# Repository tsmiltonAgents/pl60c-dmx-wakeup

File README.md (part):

# PL60C DMX wake-up lamp controller

A small ESP32-S3 board that drives the wired DMX512 input of a **Neewer PL60C** panel light so the
light can be ramped up slowly in the morning (sunrise alarm). Rev A, 2026-09-02.

Everything in this repository is generated by scripts (`./build.sh`): schematic, PCB, autorouting,
design-rule checks, Gerbers, and the JLCPCB BOM / pick-and-place files. The design passes KiCad ERC and
DRC with zero errors, the schematic and PCB netlists are cross-checked against the single source of
truth (`hw/design.py`), and every part number has been verified in stock on LCSC/JLCPCB.

| | |
|---|---|
| Board | 80 x 54 mm, 2 layers, 1.6 mm FR-4, all parts on the top side |
| MCU | ESP32-S3-WROOM-1-N16R8 (Wi-Fi + BLE, native USB) |
| DMX out | 5-pin XLR female (Neutrik NC5FAH) **and** a 3-way screw terminal for a pigtail |
| Power | USB-C, 5 V, 1 A resettable fuse, 3.3 V LDO |
| UI | RESET, BOOT, USER buttons, WS2812B RGB status LED, magnetic buzzer (alarm fallback) |
| Extras | I2C/GPIO expansion header (RTC, light sensor), UART0 header |
| Files to order | `production/pl60c_dmx_gerbers.zip`, `production/pl60c_dmx_bom_jlcpcb.csv`, `production/pl60c_dmx_cpl_jlcpcb.csv` |
| Mini variant | 38.5 x 29 mm, 4 layers, both sides, same circuit and pin map: see section 8 and `production_mini/` |

Status: **designed, reviewed and verified in software, not yet manufactured or bench-tested.** Read the
"Before you order" section and `docs/REVIEW.md` (design review: 3 wiring/spec bugs found and fixed).

---

## 1. How the light is controlled

### 1.1 The PL60C's DMX port (verified from Neewer's manual and DMX chart)

* Connectors on the bottom edge of the lamp head: `DMX-IN` = **5-pin XLR male** panel socket,
  `DMX-OUT` = 5-pin XLR female (pass-through for daisy-chaining).
* Pinout: pin 1 = signal common (0 V), pin 2 = Data−, pin 3 = Data+, pins 4 and 5 unused.
* Enable DMX on the light: long-press MODE/MENU, set `DMX ON/OFF` = ON, then `DMX ADDR` (001–512, default 1).
* On loss of the DMX signal the light **holds the last look** (no timeout). The controller must therefore
  keep streaming frames; when you want the light off, send intensity 0 rather than stopping the stream.
* No RDM support is documented. The port is not documented as isolated.

This board is the DMX **transmitter**, so it has a 5-pin XLR **female** socket (ANSI E1.11 convention).
A normal 5-pin DMX cable (male–female) goes from this board to the light's `DMX-IN`.

### 1.2 PL60C channel map (one fixed personality)

Channel numbers are relative to the DMX start address `n` set on the light. Channel `n` selects the mode,
`n+1` is always intensity, the rest depend on the mode. The FX mode uses up to 9 channels, so treat the
light as a 9-channel fixture.

| ch n value | Mode | n+1 | n+2 | n+3 | n+4 … n+8 |
|---|---|---|---|---|---|
| 0–31 | **CCT** | Intensity 0–100 % | Colour temperature 2500–10000 K | G/M −50…+50 | – |
| 32–63 | HSI | Intensity | Hue 0–360° | Saturation 0–100 % | – |
| 64–95 | FX | Intensity | Effect select | effect parameters | effect parameters |
| 96–127 | GEL | Intensity | Gel brand | Gel index | – |
| 128–159 | RGBCW | Intensity | Red | Green | Blue, Cool white, Warm white |
| 160–191 | XY | Intensity | x | y | – |

For a sunrise, CCT mode is the natural choice: ramp `n+1` from 0 to the target and, if you like, sweep
`n+2` from warm (2500 K) towards neutral as the intensity rises. Sources are listed at the end.

### 1.3 DMX512 on the wire

DMX512 is EIA-485 at 250 kbit/s, 8 data bits, no parity, 2 stop bits. A frame is: BREAK (≥ 92 µs, use
176 µs) → MARK-AFTER-BREAK (≥ 12 µs) → start code 0x00 → up to 512 slot bytes, then repeat at roughly
40–44 Hz. Data+ (pin 3) is the RS-485 **A** line, Data− (pin 2) is **B**, pin 1 is the common. A 120 Ω
terminator belongs only at the far end of the cable (the last fixture), never at the transmitter.

---

## 2. Hardware design

Full-size PDF: `production/pl60c_dmx_schematic.pdf`.

### 2.1 Blocks

**USB-C input and 3.3 V rail.** 16-pin USB-C receptacle (HRO TYPE-C-31-M-12) with 5.1 kΩ CC pull-downs
so any USB-C charger or host supplies 5 V. A 1 A hold / 1.8 A trip PTC (F1) protects the board, a
USBLC6-2SC6 (U4) clamps ESD on D+/D−/VBUS, and an AMS1117-3.3 (U2, 1 A) makes 3.3 V with 10 µF on both
sides. Budget: ESP32-S3 Wi-Fi peaks ≈ 0.5 A, buzzer ≈ 0.1 A average, LED < 60 mA.

**ESP32-S3-WROOM-1-N16R8 (U1).** 16 MB flash, 8 MB PSRAM, on-module PCB antenna. The antenna end of the
module hangs 6 mm past the top board edge, which is Espressif's preferred placement (no copper anywhere
near the antenna). USB D+/D− go straight to GPIO20/GPIO19: the S3's built-in USB-Serial/JTAG gives
programming, console and debugging with no bridge chip. EN has the standard 10 kΩ + 1 µF reset delay and
the RESET button; GPIO0 has a 10 kΩ pull-up and the BOOT button (hold BOOT, tap RESET to force the
ROM downloader, or just use `esptool` over USB which does it automatically).

**DMX transmitter (U3, SP3485EN).** 3.3 V RS-485 half-duplex transceiver, pin-compatible with MAX3485.
DI ← GPIO17 (UART TX), RO → GPIO18 (UART RX), DE and /RE tied together to GPIO16 with a 10 kΩ pull-down,
so the line is only driven once firmware asserts DE (keeps the bus quiet during boot/flash). A → XLR
pin 3 (Data+), B → XLR pin 2 (Data−), XLR pin 1 → GND. A PSM712 asymmetric TVS array (D1, +12 V / −7 V,
the RS-485 standard part) clamps surges on both lines. R6 (120 Ω) is fitted **only** if you ever want this
board to terminate a line; it is marked DNP and JLCPCB will not place it. The same three signals are on
screw terminal J3 (GND, D−, D+) so you can wire a cable pigtail instead of using the XLR.

**User interface.** WS2812B-2020-V6 RGB LED (D2) on GPIO48 through 330 Ω, powered from 3.3 V (the V6
silicon is specified for 3.3 V supply, VIH = 0.55 VDD). USER button on GPIO5 with a 10 kΩ pull-up
(snooze / manual on). Magnetic buzzer BZ1 (MLT-8530, passive, 2.7 kHz resonant, 16 Ω) driven from the
5 V rail through a 10 Ω series resistor (R10, limits the coil to its 3.6 V rating) by an S8050 NPN (Q1,
SOT-23, base via 470 Ω from GPIO6) with a B5819W Schottky flyback diode (D3) across the coil.

**Expansion.** J4: 3V3, GND, GPIO8 (SDA), GPIO9 (SCL), GPIO10, GPIO11 (e.g. a DS3231 RTC or an ambient
light sensor). J5: 3V3, GND, GPIO43 (TXD0), GPIO44 (RXD0). Four M3 mounting holes.

### 2.2 Pin map (also in `firmware/pins.h`)

| Function | GPIO | Notes |
|---|---|---|
| DMX TX (SP3485 DI) | 17 | UART1 TX |
| DMX RX (SP3485 RO) | 18 | UART1 RX, only for RDM/monitoring |
| DMX DE / /RE | 16 | HIGH = transmit; 10 kΩ pull-down |
| USB D− / D+ | 19 / 20 | native USB-Serial/JTAG |
| BOOT button | 0 | active low, strapping pin |
| USER button | 5 | active low, 10 kΩ pull-up |
| WS2812B data | 48 | 330 Ω series, LED at 3.3 V |
| Buzzer | 6 | NPN low-side switch, PWM 2.7 kHz |
| I2C SDA / SCL | 8 / 9 | header J4 |
| Spare | 10 / 11 | header J4 |
| UART0 TX / RX | 43 / 44 | header J5 |

Unused module pins are left unconnected. GPIO35–37 are reserved by the octal PSRAM of the R8 module
and GPIO3/45/46 are strapping pins; none of them is used.

### 2.3 Layout

USB-C on the left edge, XLR on the right edge with its flange over the board edge, buttons and the LED
along the bottom edge for an enclosure front panel, the terminal block also on the bottom edge.
Ground pours on both layers with stitching vias, 0.25 mm signal tracks, 0.4 mm power tracks,
0.15 mm clearance, 0.7 / 0.35 mm vias: all comfortably inside JLCPCB's 2-layer capability.
The USB-C data-pair escape is hand-routed (the router cannot do the D+/D− pair swap at 0.5 mm pitch);
the rest is autorouted by Freerouting and then checked by KiCad DRC.

---

## 3. Firmware guidance (no firmware is included, by design)

The hardware was designed so that the standard **[esp_dmx](https://github.com/someweisguy/esp_dmx)**
library works unmodified: `dmx_set_pin(DMX_NUM_1, PIN_DMX_TX, PIN_DMX_RX, PIN_DMX_DE)` and then
`dmx_write()` + `dmx_send()` at 40–44 Hz. It handles the break/MAB timing with the UART hardware.

Suggested behaviour:

1. Boot, connect to Wi-Fi, sync time by SNTP (add a DS3231 on J4 if you want time without Wi-Fi).
2. Stream a DMX frame continuously (44 Hz). Idle: `ch1 = 0` (CCT mode), `ch2 = 0` (intensity 0).
   Never stop the stream: the PL60C holds the last look on signal loss.
3. Sunrise: over 20–30 min raise `ch2` from 0 → target with a perceptual (gamma ≈ 2.2) curve, optionally
   sweep `ch3` from 2500 K towards 4000–5600 K. After the ramp hold, then optionally sound the buzzer
   (2.7 kHz square wave on GPIO6, 50 % duty, short beeps) until USER is pressed.
4. USER button: short press = snooze / cancel, long press = manual light toggle. BOOT can be a second
   button after boot. RGB LED: breathing colours for state (idle / ramping / alarm / no Wi-Fi).
5. Set the light's `DMX ADDR` to 1 so the controller's channels 1–9 map directly.

Provisioning, OTA and a web UI are the usual ESP-IDF / Arduino-ESP32 fare; the S3's USB CDC console is
available on the USB-C port without any extra hardware.

---

## 4. Ordering from JLCPCB

Files in `production/`:

| File | Purpose |
|---|---|
| `pl60c_dmx_gerbers.zip` | Gerber RS-274X (Protel extensions) + Excellon drills, JLCPCB settings |
| `pl60c_dmx_bom_jlcpcb.csv` | BOM in JLCPCB format (Comment, Designator, Footprint, LCSC Part #) |
| `pl60c_dmx_cpl_jlcpcb.csv` | Pick-and-place, rotations corrected with the JLCKicadTools database |
| `pl60c_dmx_cpl_kicad_rotation.csv` | Same, with raw KiCad rotations, in case the preview shows parts turned |
| `pl60c_dmx_bom_full.csv` | Engineering BOM incl. DNP and mechanical parts |
| `pl60c_dmx_schematic.pdf`, `pl60c_dmx_pcb_top.pdf`, `pl60c_dmx_pcb_bottom.pdf`, `pl60c_dmx.step` | documentation / mechanical |

Steps:

1. jlcpcb.com → *Order now* → upload `pl60c_dmx_gerbers.zip`. Options: 2 layers, 80 x 54 mm, 1.6 mm,
   any colour, HASL (lead-free) or ENIG, 1 oz copper, "Remove order number: specify location" is not
   needed (no marker placed; choose "Yes" if you dislike the number).
2. Turn on **PCB Assembly**, top side, then upload `pl60c_dmx_bom_jlcpcb.csv` and
   `pl60c_dmx_cpl_jlcpcb.csv`.
3. In the parts step all 25 BOM lines resolve to the LCSC numbers below. R6 is intentionally absent (DNP).
4. **Check the placement preview carefully** for rotation of U2 (SOT-223), U3 (SOIC-8), D1/Q1 (SOT-23),
   J1 (USB-C), D2 (WS2812B), J2 (XLR) and J3 (terminal). JLCPCB's orientation conventions differ from
   KiCad's per package; if any polarised part looks turned, re-upload
   `pl60c_dmx_cpl_kicad_rotation.csv` or rotate it in their editor. Pin 1 of the module is the
   top-left pad when the antenna points up.
5. Through-hole parts (XLR, terminal block, headers) are "extended" parts assembled by hand at JLCPCB;
   they add a small per-part fee. If you prefer, delete J2/J3/J4/J5 from the BOM and solder them yourself.

### 4.1 Bill of materials (all verified in stock on LCSC on 2026-09-02, `tools/check_lcsc.py`)

| Ref | Part | LCSC | JLC type |
|---|---|---|---|
| U1 | ESP32-S3-WROOM-1-N16R8 | C2913202 | extended |
| U2 | AMS1117-3.3, SOT-223 | C6186 | basic |
| U3 | SP3485EN-L/TR, SOIC-8 | C8963 | basic |
| U4 | USBLC6-2SC6, SOT-23-6 | C7519 | extended |
| D1 | PSM712-LF-T7 TVS, SOT-23 | C32677 | basic |
| D2 | WS2812B-2020-V6 RGB LED | C52917434 | extended |
| D3 | B5819W Schottky, SOD-123 | C8598 | basic |
| Q1 | S8050 NPN, SOT-23 (B-E-C) | C2146 | basic |
| F1 | PTC 1 A hold, 1206 | C5358568 | extended |
| J1 | USB-C 16P, HRO TYPE-C-31-M-12 | C165948 | extended |
| J2 | Neutrik NC5FAH XLR-5 female, PCB horizontal | C368501 | extended (low stock, ~130) |
| J3 | KF128-5.08-3P screw terminal | C474953 | extended |
| J4 / J5 | 2.54 mm headers 1x6 / 1x4 | C37208 / C124378 | extended |
| SW1–SW3 | TS-1187A-B-A-B tactile 5.1 mm | C318884 | basic |
| BZ1 | MLT-8530 magnetic buzzer | C94599 | extended |
| C1, C4 | 10 µF 25 V 0805 | C15850 | basic |
| C2 | 22 µF 25 V 0805 | C45783 | basic |
| R10 | 10 Ω 1206 250 mW | C17903 | basic |
| C6 | 1 µF 50 V 0805 | C28323 | basic |
| C3, C5, C7, C8 | 100 nF 50 V 0603 | C14663 | basic |
| R1, R2 | 5.1 kΩ 0603 | C23186 | basic |
| R3, R4, R5, R7 | 10 kΩ 0603 | C25804 | basic |
| R8 | 330 Ω 0603 | C23138 | basic |
| R9 | 470 Ω 0603 | C23179 | basic |
| R6 | 120 Ω 0603, **DNP** | C22787 | – |

If the NC5FAH is out of stock: CAX **XLR-5M-24WP** (C53431204, same NC5FAH footprint, female despite the
name) or order the Neutrik separately and hand-solder it. Rough parts cost per board is about USD 15
(ESP32 ≈ 5, XLR ≈ 6), plus JLCPCB's PCB and assembly fees.

### 4.2 Before you order

* This is a rev A that has only been verified by simulation-free checks (ERC, DRC, netlist, Gerber
  review, part stock). The circuit follows Espressif's and the transceiver vendor's reference designs
  closely, but a first build should be treated as a prototype.
* The DMX port is **not galvanically isolated** (same as most hobby DMX interfaces). The PL60C runs from
  its own 19.6 V PSU; keep the controller on a separate USB supply and you have a normal
  ground-referenced link, which is how the light's own wired console connection works. An isolated
  variant (ADM2483 + B0505S) would add ~USD 7 and a second transceiver footprint; not done in rev A.
* USB-C receptacle mechanical: the connector body is placed with its front lip 0.55 mm proud of the
  board edge, per the HRO drawing. Check it against your enclosure.

---

## 5. Hooking it up

1. Flash firmware over the USB-C port (native USB, no driver hassle on macOS/Linux).
2. Cable: 5-pin XLR male → female DMX cable from this board's `DMX OUT` to the light's `DMX-IN`.
   Or wire a cable to J3: `GND` → XLR pin 1, `D−` → pin 2, `D+` → pin 3.
3. On the light: `DMX ON`, `DMX ADDR = 001`.
4. If the light is the only fixture and the cable is longer than a few metres, fit a 120 Ω terminator
   plug in the light's `DMX-OUT`. Do not fit R6 on this board.

---

## 6. What was verified

| Check | Result |
|---|---|
| Design review against datasheets (`docs/REVIEW.md`) | 14 items; 3 bugs found and fixed (SOT-23 transistor pinout, LED supply spec, buzzer overdrive) |
| KiCad ERC on the generated schematic | 0 findings |
| Schematic netlist vs `hw/design.py` | 27/27 nets identical |
| PCB pad-to-net vs `hw/design.py` | 27/27 nets identical |
| KiCad DRC (clearance 0.15 mm, edge 0.3 mm, hole-to-hole 0.5 mm, courtyards, silkscreen) | 0 errors; 6 warnings, all "silkscreen clipped by board edge" from the three connectors that deliberately overhang the edge |
| Unrouted connections | 0 |
| Gerbers rendered independently with gerbv (copper, silk, mask, paste, outline, drills) | match the KiCad board, see `docs/gerber_*_check.png` |
| Drill file | 151 plated + 8 non-plated holes, smallest 0.30 mm (module thermal vias enlarged from the library's 0.2 mm to suit JLCPCB) |
| LCSC stock / package for every part number | all in stock, packages match footprints (`tools/check_lcsc.py`) |
| Datasheets checked against footprints | TS-1187A vs Alps SKQG land pattern, MLT-8530 pad layout, KF128 pin size (holes set to 1.4 mm), NC5FAH (KiCad footprint is for this exact part) |

---

## 7. Repository layout and regenerating

```
hw/design.py        single source of truth: parts, LCSC numbers, nets, schematic and PCB placement
hw/design_mini.py   the MINI variant (same circuit, different parts/placement); hw/variant.py selects it
hw/gen_sch.py       KiCad 10 schematic writer (labels + power symbols, ERC-clean)
hw/gen_pcb.py       pcbnew script: board outline, footprints, nets, rules, pours, GND stitching, USB escape
hw/route.py         Freerouting driver (DSN export, autoroute, SES import, zone fill)
hw/fix_gnd.py       post-route ground fixer + dangling via cleanup
tools/export.py     Gerbers/drill, JLCPCB BOM + CPL, PDFs, renders, STEP
tools/verify_*.py   netlist consistency checks
tools/check_lcsc.py live stock check of every LCSC part number
pcb/                the generated KiCad project (open pl60c_dmx.kicad_pro in KiCad 10)
production/         everything JLCPCB needs
docs/               images used in this README
firmware/pins.h     pin map and DMX constants for the firmware author
build.sh            full pipeline; autocommit.sh commits and pushes every 2 minutes
```

Regenerate with `./build.sh` (rev A) or `./build.sh mini`. Requirements: KiCad 10.0.x app bundle at `/Applications/KiCad`
(its bundled Python is used for `pcbnew`), Java 25+ (`brew install openjdk`) and
`tools/freerouting.jar` (Freerouting 2.3.0, download from its GitHub releases), plus `gerbv` if you want
the Gerber check images. Edit `hw/design.py`, never the KiCad files (they are overwritten).

---

## 8. MINI variant (38.5 x 29 mm, 4 layers, both sides)

Same circuit, same GPIO map, one quarter of the area (1120 mm² vs 4320 mm²). Files: `production_mini/`
(`pl60c_dmx_mini_gerbers.zip`, `pl60c_dmx_mini_bom_jlcpcb.csv`, `pl60c_dmx_mini_cpl_jlcpcb.csv`),
KiCad project `pcb/pl60c_dmx_mini.*`, source `hw/design_mini.py`, build with `./build.sh mini`.

What changed to get there:

| | rev A | mini |
|---|---|---|
| Module | ESP32-S3-WROOM-1-N16R8 (18 x 25.5 mm) | **ESP32-S3-MINI-1-N8** (15.4 x 20.5 mm, C2913206), antenna off the left edge |
| Layers / sides | 2 layers, top only | **4 layers** (JLC04161H-7628 stack: signal, solid GND plane, signal + GND pour, signal), parts on **both sides** |
| XLR-5 female | on board | **on board** (Neutrik NC5FAH, right edge; its flange holes mount the board) |
| Passives | 0603 / 0805 | **0402** (all JLCPCB Basic), 10 µF in 0603 |
| LDO | AMS1117 SOT-223 | **AP2112K-3.3** SOT-23-5, 600 mA (C51118) |
| RGB LED | WS2812B-2020-V6 | same |
| Buttons | RESET, BOOT, USER (5.1 mm) | **BOOT, USER** (3.9 x 3 mm TS-1088, Basic); reset = re-plug USB or EN via the 10 k/1 µF network |
| Buzzer | on board | **off board**: driver kept (S8050 + 10 Ω + flyback), solder a passive magnetic buzzer to the `BZ+`/`BZ-` pads |
| Pigtail terminal, headers, mounting holes | yes | dropped; I2C expansion on 4 test pads (`3V3 GND SDA SCL`), UART0 not brought out (USB console) |
| PTC | 1 A 1206 | same |

Top side: module, USB-C, XLR, two buttons, RGB LED. Bottom side: everything else. The USB-C body
protrudes 0.55 mm from the bottom edge, the XLR flange protrudes from the right edge, and the module
antenna hangs 4.5 mm off the left edge, so the enclosure needs cut-outs on three sides.

Verification, same procedure as rev A: ERC 0 findings, schematic and PCB netlists identical to the design
(23 nets), 0 unrouted, DRC 0 errors (6 "silkscreen clipped by edge" warnings from the overhanging parts
and one dangling stub warning inside the hand-routed USB escape), Gerbers for all four copper layers
rendered and checked with gerbv (`docs/mini_gerber_*_check.png`), every LCSC part in stock
(`PL60C_VARIANT=mini python3 tools/check_lcsc.py`). JLCPCB rules used: 0.1 mm min track/clearance
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
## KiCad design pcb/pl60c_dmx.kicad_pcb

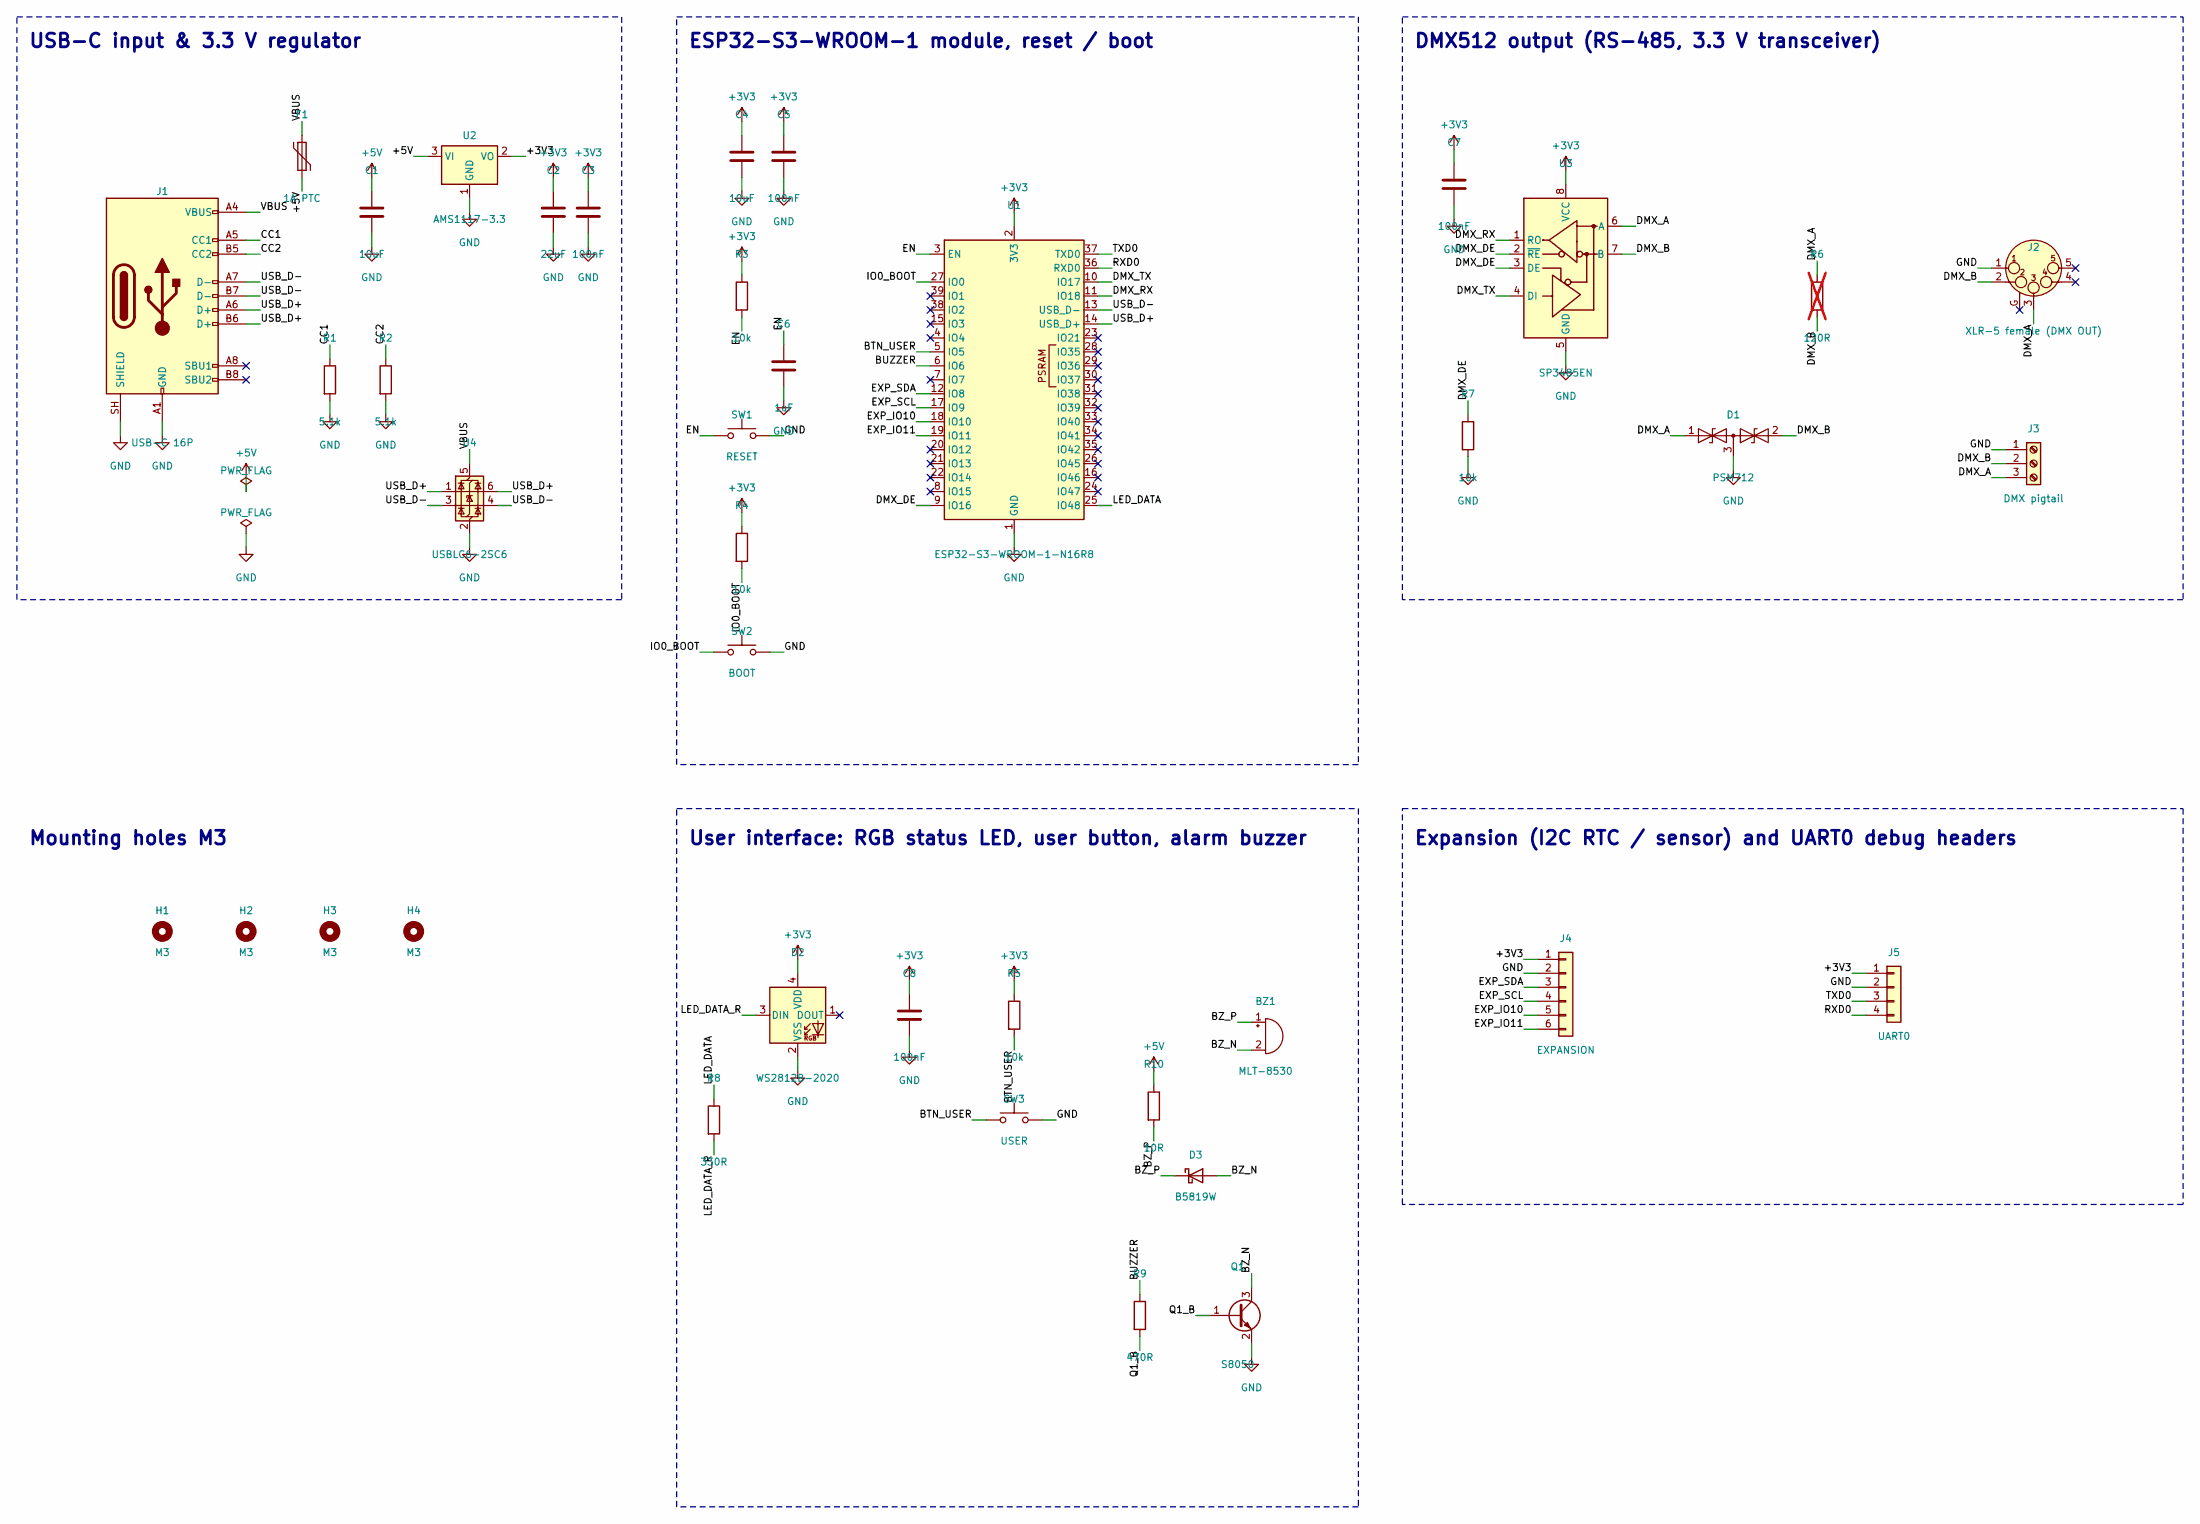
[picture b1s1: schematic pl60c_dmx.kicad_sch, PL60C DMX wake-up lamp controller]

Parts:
BZ1: MLT-8530; MagneticBuzzer_CUI_CMT-8504-100-SMT; MPN MLT-8530; LCSC C94599
C1, C4: 10uF; C_0805_2012Metric; LCSC C15850
C2: 22uF; C_0805_2012Metric; LCSC C45783
C3, C5, C7, C8: 100nF; C_0603_1608Metric; LCSC C14663
C6: 1uF; C_0805_2012Metric; MPN CL21B105KBFNNNE; LCSC C28323
D1: PSM712; SOT-23; MPN PSM712-LF-T7; LCSC C32677
D2: WS2812B-2020; LED_WS2812B-2020_PLCC4_2.0x2.0mm; MPN WS2812B-2020-V6; LCSC C52917434
D3: B5819W; D_SOD-123; MPN B5819W SL; LCSC C8598
F1: 1A PTC; Fuse_1206_3216Metric; MPN BSMD1206-100-30V; LCSC C5358568
H1, H2, H3, H4: M3; MountingHole_3.2mm_M3
J1: USB-C 16P; USB_C_Receptacle_HRO_TYPE-C-31-M-12; MPN TYPE-C-31-M-12; LCSC C165948
J2: XLR-5 female (DMX OUT); Jack_XLR_Neutrik_NC5FAH_Horizontal; MPN NC5FAH; LCSC C368501
J3: DMX pigtail; TerminalBlock_Phoenix_MKDS-1,5-3-5.08_1x03_P5.08mm_Horizont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; MPN KF128-5.08-3P-AA; LCSC C474953
J4: EXPANSION; PinHeader_1x06_P2.54mm_Vertical; MPN 2.54-1x6P; LCSC C37208
J5: UART0; PinHeader_1x04_P2.54mm_Vertical; MPN B-2100S04P-A110; LCSC C124378
Q1: S8050; SOT-23; MPN S8050; LCSC C2146
R1, R2: 5.1k; R_0603_1608Metric; LCSC C23186
R3, R4, R5, R7: 10k; R_0603_1608Metric; LCSC C25804
R6: 120R; R_0603_1608Metric; LCSC C22787; not fitted
R8: 330R; R_0603_1608Metric; LCSC C23138
R9: 470R; R_0603_1608Metric; LCSC C23179
R10: 10R; R_1206_3216Metric; LCSC C17903
SW1: RESET; SW_SPST_SKQG_WithStem; MPN TS-1187A-B-A-B; LCSC C318884
SW2: BOOT; SW_SPST_SKQG_WithStem; MPN TS-1187A-B-A-B; LCSC C318884
SW3: USER; SW_SPST_SKQG_WithStem; MPN TS-1187A-B-A-B; LCSC C318884
U1: ESP32-S3-WROOM-1-N16R8; ESP32-S3-WROOM-1; MPN ESP32-S3-WROOM-1-N16R8; LCSC C2913202
U2: AMS1117-3.3; SOT-223-3_TabPin2; MPN AMS1117-3.3; LCSC C6186
U3: SP3485EN; SOIC-8_3.9x4.9mm_P1.27mm; MPN SP3485EN-L/TR; LCSC C8963
U4: USBLC6-2SC6; SOT-23-6; MPN USBLC6-2SC6; LCSC C7519

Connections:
+3V3: C2.1, C3.1, C4.1, C5.1, C7.1, C8.1, D2.4 (VDD), J4.1, J5.1, R3.1, R4.1, R5.1, U1.2 (3V3), U2.2 (VO), U3.8 (VCC)
+5V: C1.1, F1.2, R10.1, U2.3 (VI)
BTN_USER: R5.2, SW3.1, U1.5 (IO5)
BUZZER: R9.1, U1.6 (IO6)
BZ_N: BZ1.2 (-), D3.2 (A), Q1.3 (C)
BZ_P: BZ1.1 (+), D3.1 (K), R10.2
CC1: J1.A5 (CC1), R1.1
CC2: J1.B5 (CC2), R2.1
DMX_A: D1.1 (A1), J2.3, J3.3, R6.1, U3.6 (A)
DMX_B: D1.2 (A2), J2.2, J3.2, R6.2, U3.7 (B)
DMX_DE: R7.1, U1.9 (IO16), U3.2 (~RE), U3.3 (DE)
DMX_RX: U1.11 (IO18), U3.1 (RO)
DMX_TX: U1.10 (IO17), U3.4 (DI)
EN: C6.1, R3.2, SW1.1, U1.3 (EN)
EXP_IO10: J4.5, U1.18 (IO10)
EXP_IO11: J4.6, U1.19 (IO11)
EXP_SCL: J4.4, U1.17 (IO9)
EXP_SDA: J4.3, U1.12 (IO8)
GND: C1.2, C2.2, C3.2, C4.2, C5.2, C6.2, C7.2, C8.2, D1.3 (common), D2.2 (VSS), J1.A1 (GND), J1.A12 (GND), J1.B1 (GND), J1.B12 (GND), J1.SH (SHIELD), J2.1, J3.1, J4.2, J5.2, Q1.2 (E), R1.2, R2.2, R7.2, SW1.2, SW2.2, SW3.2, U1.1 (GND), U1.40 (GND), U1.41 (GND), U2.1 (GND), U3.5 (GND), U4.2 (GND)
IO0_BOOT: R4.2, SW2.1, U1.27 (IO0)
LED_DATA: R8.1, U1.25 (IO48)
LED_DATA_R: D2.3 (DIN), R8.2
Q1_B: Q1.1 (B), R9.2
RXD0: J5.4, U1.36 (RXD0)
TXD0: J5.3, U1.37 (TXD0)
USB_D+: J1.A6 (D+), J1.B6 (D+), U1.14 (USB_D+), U4.1 (I/O1), U4.6 (I/O1)
USB_D-: J1.A7 (D-), J1.B7 (D-), U1.13 (USB_D-), U4.3 (I/O2), U4.4 (I/O2)
VBUS: F1.1, J1.A4 (VBUS), J1.A9 (VBUS), J1.B4 (VBUS), J1.B9 (VBUS), U4.5 (VBUS)

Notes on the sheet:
USB-C input & 3.3 V regulator
ESP32-S3-WROOM-1 module, reset / boot
DMX512 output (RS-485, 3.3 V transceiver)
User interface: RGB status LED, user button, alarm buzzer
Expansion (I2C RTC / sensor) and UART0 debug headers
Mounting holes M3

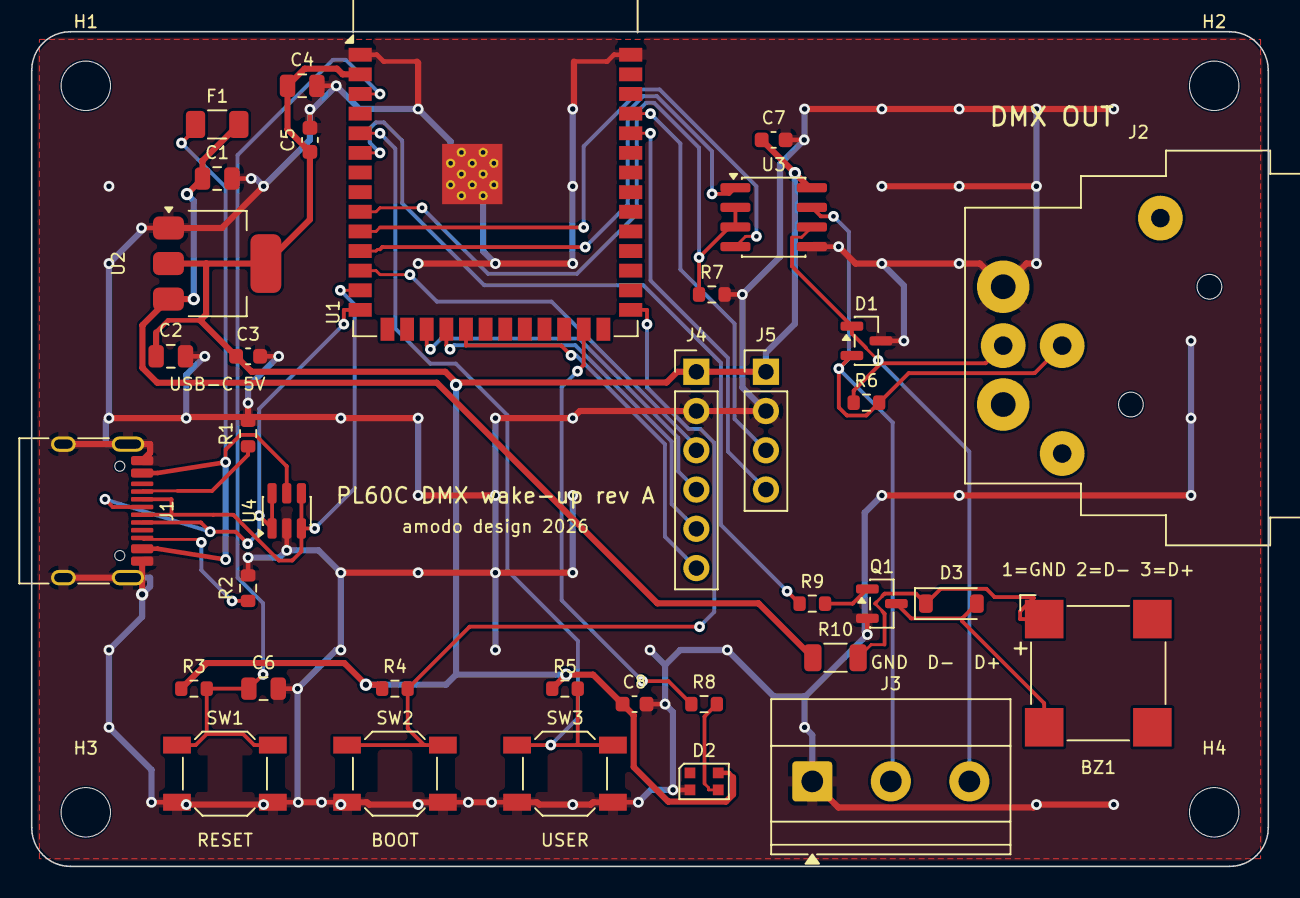
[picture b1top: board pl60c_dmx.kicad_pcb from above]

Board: 2 copper layers, 80.0 x 54.0 mm, 40 parts (0 on the bottom side), 28 nets.

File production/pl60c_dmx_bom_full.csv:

Ref,Value,MPN,LCSC,Footprint,DNP,Description
BZ1,MLT-8530,MLT-8530,C94599,Buzzer_Beeper:MagneticBuzzer_CUI_CMT-8504-100-SMT,,"Magnetic buzzer 8.5x8.5 mm SMD, passive, 16 ohm, drive 2.7 kHz square wave"
C1,10uF,,C15850,Capacitor_SMD:C_0805_2012Metric,,10uF 25V X5R 0805
C2,22uF,,C45783,Capacitor_SMD:C_0805_2012Metric,,"22uF 25V X5R 0805 (AMS1117 output, datasheet asks for >=22uF)"
C3,100nF,,C14663,Capacitor_SMD:C_0603_1608Metric,,100nF 50V X7R 0603
C4,10uF,,C15850,Capacitor_SMD:C_0805_2012Metric,,10uF 25V X5R 0805
C5,100nF,,C14663,Capacitor_SMD:C_0603_1608Metric,,100nF 50V X7R 0603
C6,1uF,CL21B105KBFNNNE,C28323,Capacitor_SMD:C_0805_2012Metric,,1uF 50V X7R 0805 (EN reset delay)
C7,100nF,,C14663,Capacitor_SMD:C_0603_1608Metric,,100nF 50V X7R 0603
C8,100nF,,C14663,Capacitor_SMD:C_0603_1608Metric,,100nF 50V X7R 0603
D1,PSM712,PSM712-LF-T7,C32677,Package_TO_SOT_SMD:SOT-23,,RS-485 TVS array +12/-7 V 600 W SOT-23
D2,WS2812B-2020,WS2812B-2020-V6,C52917434,LED_SMD:LED_WS2812B-2020_PLCC4_2.0x2.0mm,,"Addressable RGB LED 2x2 mm, V6 silicon: 3.3 V supply supported, VIH = 0.55 VDD (datasheet)"
D3,B5819W,B5819W SL,C8598,Diode_SMD:D_SOD-123,,Schottky flyback diode 1 A 40 V SOD-123
F1,1A PTC,BSMD1206-100-30V,C5358568,Fuse:Fuse_1206_3216Metric,,"PTC resettable fuse 1206, 1 A hold / 1.8 A trip, 30 V"
H1,M3,,,MountingHole:MountingHole_3.2mm_M3,,Mounting hole M3
H2,M3,,,MountingHole:MountingHole_3.2mm_M3,,Mounting hole M3
H3,M3,,,MountingHole:MountingHole_3.2mm_M3,,Mounting hole M3
H4,M3,,,MountingHole:MountingHole_3.2mm_M3,,Mounting hole M3
J1,USB-C 16P,TYPE-C-31-M-12,C165948,Connector_USB:USB_C_Receptacle_HRO_TYPE-C-31-M-12,,"USB-C receptacle 16P, USB 2.0 (HRO TYPE-C-31-M-12)"
J2,XLR-5 female (DMX OUT),NC5FAH,C368501,Connector_Audio:Jack_XLR_Neutrik_NC5FAH_Horizontal,,"Neutrik XLR 5-pin female, horizontal PCB mount (DMX OUT)"
J3,DMX pigtail,KF128-5.08-3P-AA,C474953,"TerminalBlock_Phoenix:TerminalBlock_Phoenix_MKDS-1,5-3-5.08_1x03_P5.08mm_Horizontal",,"Screw terminal 3P 5.08 mm (alt. DMX wire output: GND, D-, D+)"
J4,EXPANSION,2.54-1x6P,C37208,Connector_PinHeader_2.54mm:PinHeader_1x06_P2.54mm_Vertical,,Pin header 1x6 2.54 mm
J5,UART0,B-2100S04P-A110,C124378,Connector_PinHeader_2.54mm:PinHeader_1x04_P2.54mm_Vertical,,Pin header 1x4 2.54 mm
Q1,S8050,S8050,C2146,Package_TO_SOT_SMD:SOT-23,,NPN 0.5A SOT-23 buzzer driver
R1,5.1k,,C23186,Resistor_SMD:R_0603_1608Metric,,5.1k 0603 1% (USB-C CC pull-down)
R2,5.1k,,C23186,Resistor_SMD:R_0603_1608Metric,,5.1k 0603 1% (USB-C CC pull-down)
R3,10k,,C25804,Resistor_SMD:R_0603_1608Metric,,10k 0603
R4,10k,,C25804,Resistor_SMD:R_0603_1608Metric,,10k 0603
R5,10k,,C25804,Resistor_SMD:R_0603_1608Metric,,10k 0603
R6,120R,,C22787,Resistor_SMD:R_0603_1608Metric,yes,120R termination - DNP (fit only if this board ends the DMX line)
R7,10k,,C25804,Resistor_SMD:R_0603_1608Metric,,10k 0603 (DE pull-down: receiver idle until firmware drives)
R8,330R,,C23138,Resistor_SMD:R_0603_1608Metric,,330R 0603 series (WS2812 data)
R9,470R,,C23179,Resistor_SMD:R_0603_1608Metric,,470R 0603 base resistor (buzzer datasheet drive circuit)
R10,10R,,C17903,Resistor_SMD:R_1206_3216Metric,,10R 1206 250mW buzzer series resistor: limits coil to ~180 mA / 2.9 V from the 5 V rail
SW1,RESET,TS-1187A-B-A-B,C318884,Button_Switch_SMD:SW_SPST_SKQG_WithStem,,Tactile switch 5.1x5.1x1.5 mm SMD
SW2,BOOT,TS-1187A-B-A-B,C318884,Button_Switch_SMD:SW_SPST_SKQG_WithStem,,Tactile switch 5.1x5.1x1.5 mm SMD
SW3,USER,TS-1187A-B-A-B,C318884,Button_Switch_SMD:SW_SPST_SKQG_WithStem,,Tactile switch 5.1x5.1x1.5 mm SMD (snooze / manual on)
U1,ESP32-S3-WROOM-1-N16R8,ESP32-S3-WROOM-1-N16R8,C2913202,RF_Module:ESP32-S3-WROOM-1,,"ESP32-S3 WiFi/BLE module, 16 MB flash + 8 MB PSRAM, PCB antenna"
U2,AMS1117-3.3,AMS1117-3.3,C6186,Package_TO_SOT_SMD:SOT-223-3_TabPin2,,LDO 3.3V 1A SOT-223
U3,SP3485EN,SP3485EN-L/TR,C8963,Package_SO:SOIC-8_3.9x4.9mm_P1.27mm,,RS-485 transceiver 3.3 V half-duplex SOIC-8 (MAX3485 pin-compatible)
U4,USBLC6-2SC6,USBLC6-2SC6,C7519,Package_TO_SOT_SMD:SOT-23-6,,USB ESD protection array

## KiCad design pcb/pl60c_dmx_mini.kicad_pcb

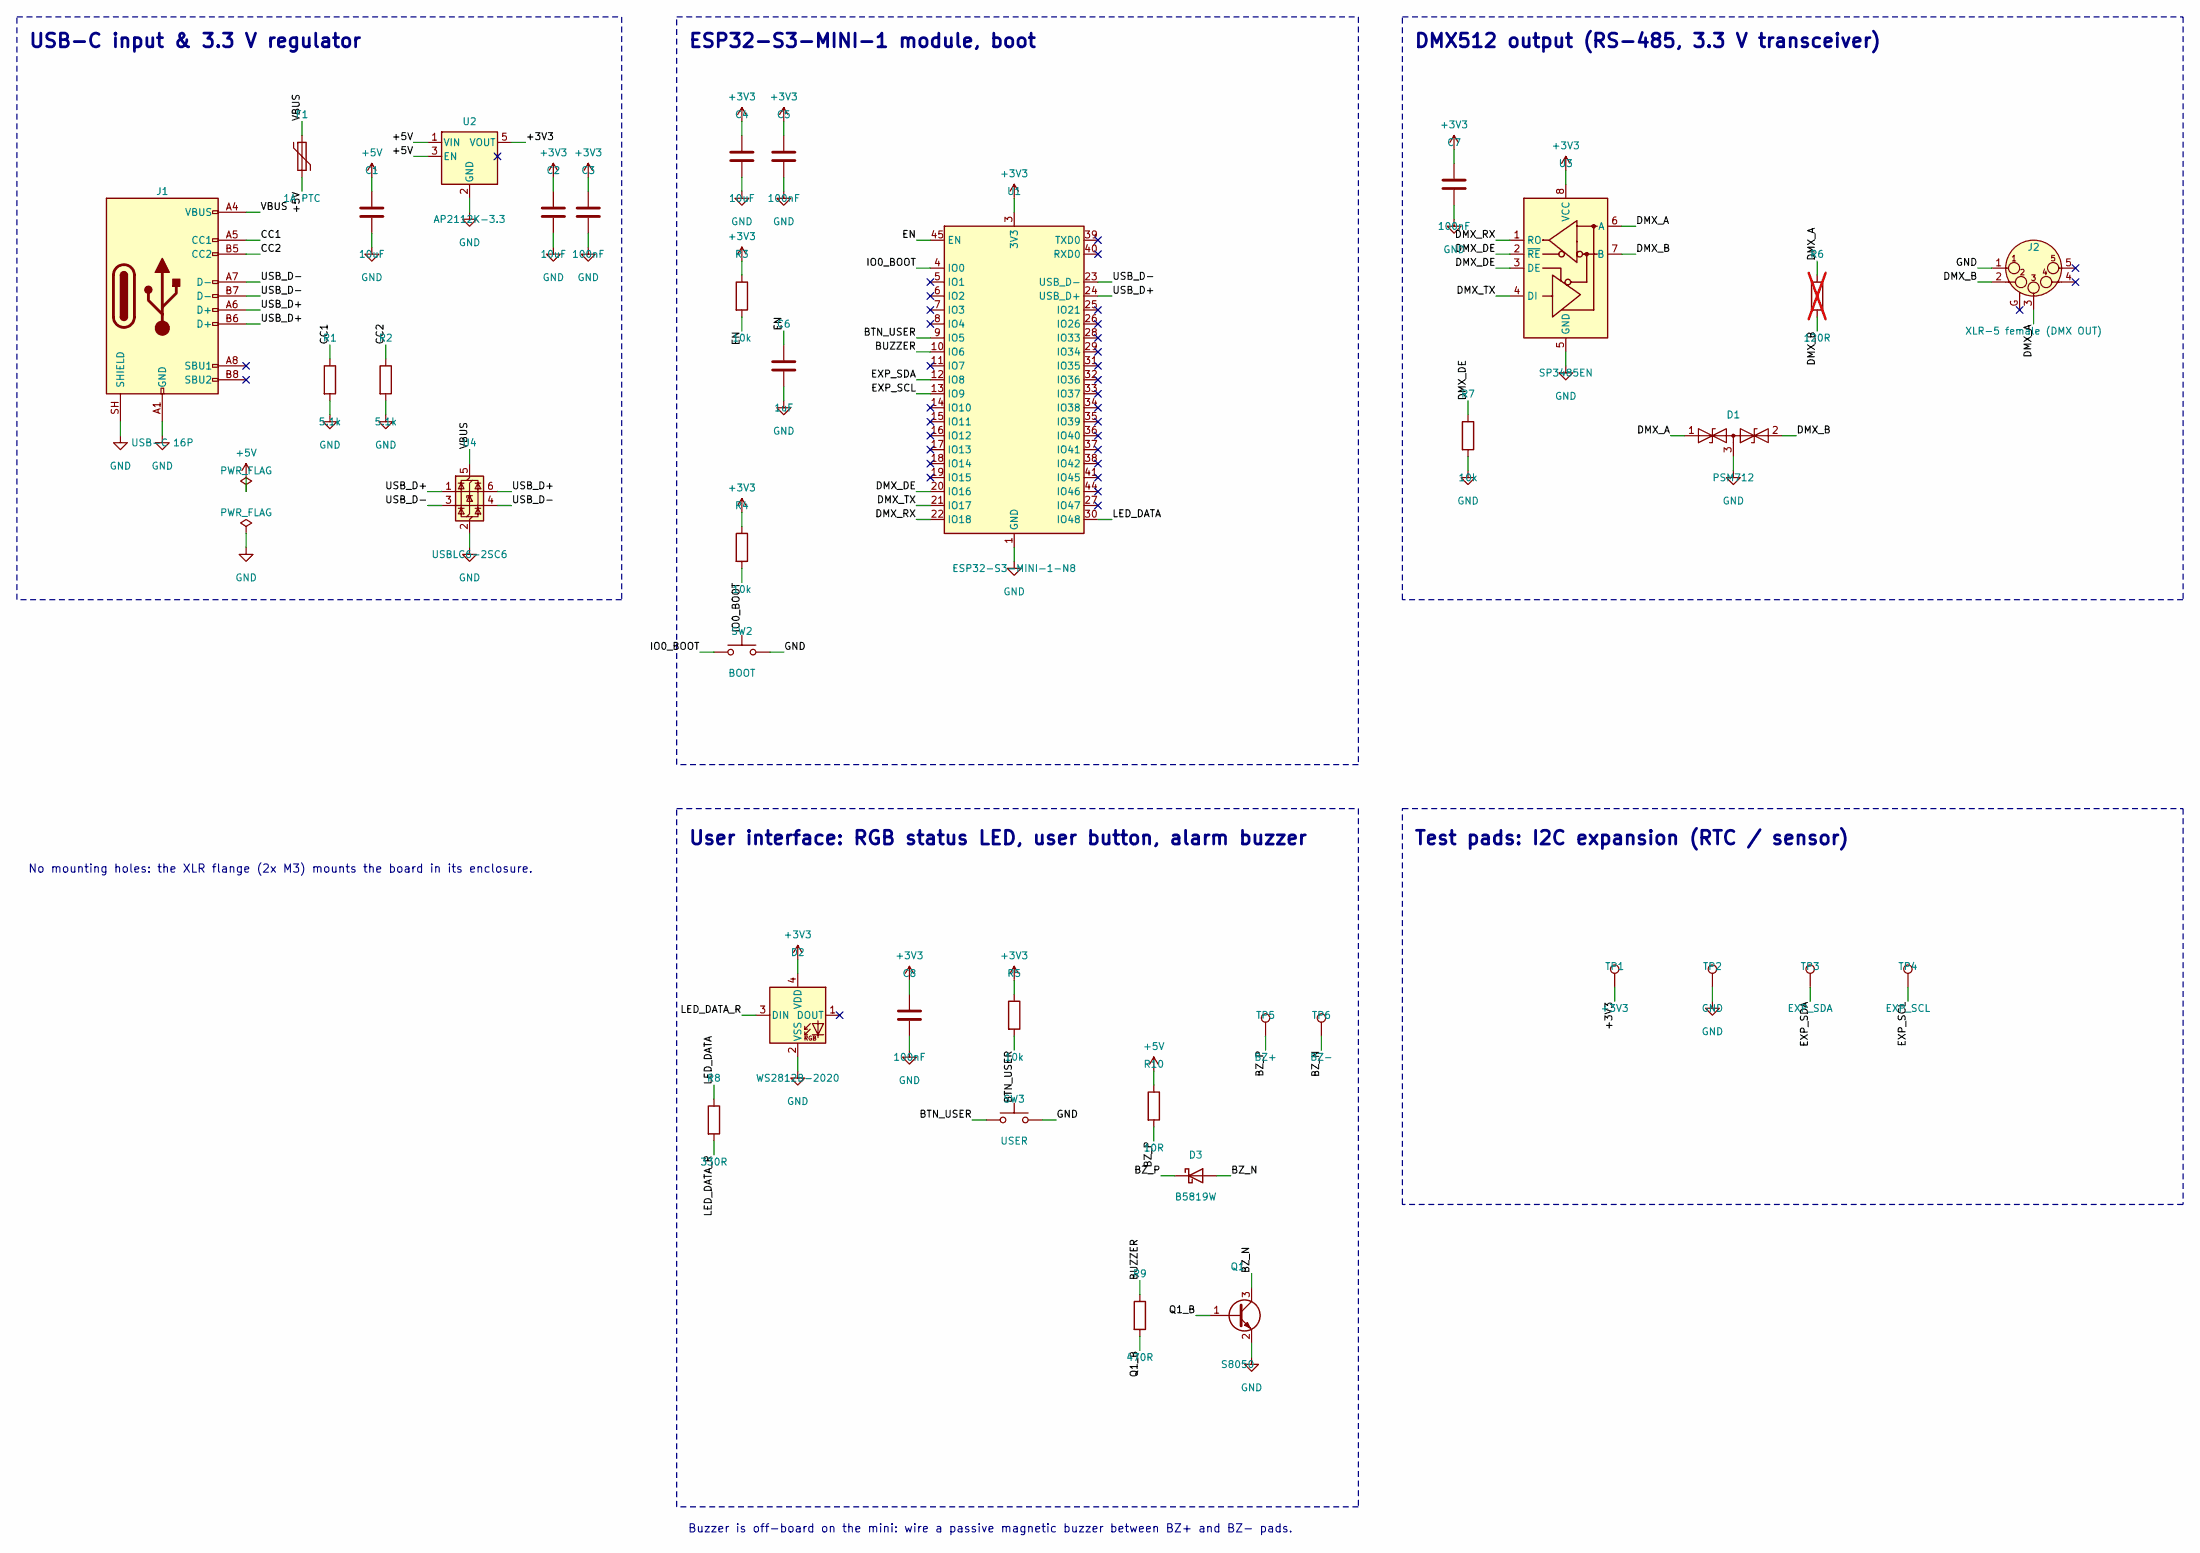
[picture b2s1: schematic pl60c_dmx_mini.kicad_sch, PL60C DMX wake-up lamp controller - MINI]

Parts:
C1, C2, C4: 10uF; C_0603_1608Metric; LCSC C19702
C3, C5, C7, C8: 100nF; C_0402_1005Metric; LCSC C1525
C6: 1uF; C_0402_1005Metric; LCSC C52923
D1: PSM712; SOT-23; MPN PSM712-LF-T7; LCSC C32677
D2: WS2812B-2020; LED_WS2812B-2020_PLCC4_2.0x2.0mm; MPN WS2812B-2020-V6; LCSC C52917434
D3: B5819W; D_SOD-123; MPN B5819W SL; LCSC C8598
F1: 1A PTC; Fuse_1206_3216Metric; MPN BSMD1206-100-30V; LCSC C5358568
J1: USB-C 16P; USB_C_Receptacle_HRO_TYPE-C-31-M-12; MPN TYPE-C-31-M-12; LCSC C165948
J2: XLR-5 female (DMX OUT); Jack_XLR_Neutrik_NC5FAH_Horizontal; MPN NC5FAH; LCSC C368501
Q1: S8050; SOT-23; MPN S8050; LCSC C2146
R1, R2: 5.1k; R_0402_1005Metric; LCSC C25905
R3, R4, R5, R7: 10k; R_0402_1005Metric; LCSC C25744
R6: 120R; R_0402_1005Metric; LCSC C25079; not fitted
R8: 330R; R_0402_1005Metric; LCSC C25104
R9: 470R; R_0402_1005Metric; LCSC C25117
R10: 10R; R_1206_3216Metric; LCSC C17903
SW2: BOOT; SW_SPST_TS-1088-xR020; MPN TS-1088-AR02016; LCSC C720477
SW3: USER; SW_SPST_TS-1088-xR020; MPN TS-1088-AR02016; LCSC C720477
TP1: +3V3; TestPoint_Pad_1.5x1.5mm
TP2: GND; TestPoint_Pad_1.5x1.5mm
TP3: EXP_SDA; TestPoint_Pad_1.5x1.5mm
TP4: EXP_SCL; TestPoint_Pad_1.5x1.5mm
TP5: BZ+; TestPoint_Pad_1.5x1.5mm
TP6: BZ-; TestPoint_Pad_1.5x1.5mm
U1: ESP32-S3-MINI-1-N8; ESP32-S2-MINI-1; MPN ESP32-S3-MINI-1-N8; LCSC C2913206
U2: AP2112K-3.3; SOT-23-5; MPN AP2112K-3.3TRG1; LCSC C51118
U3: SP3485EN; SOIC-8_3.9x4.9mm_P1.27mm; MPN SP3485EN-L/TR; LCSC C8963
U4: USBLC6-2SC6; SOT-23-6; MPN USBLC6-2SC6; LCSC C7519

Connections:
+3V3: C2.1, C3.1, C4.1, C5.1, C7.1, C8.1, D2.4 (VDD), R3.1, R4.1, R5.1, TP1.1, U1.3 (3V3), U2.5 (VOUT), U3.8 (VCC)
+5V: C1.1, F1.2, R10.1, U2.1 (VIN), U2.3 (EN)
BTN_USER: R5.2, SW3.1, U1.9 (IO5)
BUZZER: R9.1, U1.10 (IO6)
BZ_N: D3.2 (A), Q1.3 (C), TP6.1
BZ_P: D3.1 (K), R10.2, TP5.1
CC1: J1.A5 (CC1), R1.1
CC2: J1.B5 (CC2), R2.1
DMX_A: D1.1 (A1), J2.3, R6.1, U3.6 (A)
DMX_B: D1.2 (A2), J2.2, R6.2, U3.7 (B)
DMX_DE: R7.1, U1.20 (IO16), U3.2 (~RE), U3.3 (DE)
DMX_RX: U1.22 (IO18), U3.1 (RO)
DMX_TX: U1.21 (IO17), U3.4 (DI)
EN: C6.1, R3.2, U1.45 (EN)
EXP_SCL: TP4.1, U1.13 (IO9)
EXP_SDA: TP3.1, U1.12 (IO8)
GND: C1.2, C2.2, C3.2, C4.2, C5.2, C6.2, C7.2, C8.2, D1.3 (common), D2.2 (VSS), J1.A1 (GND), J1.A12 (GND), J1.B1 (GND), J1.B12 (GND), J1.SH (SHIELD), J2.1, Q1.2 (E), R1.2, R2.2, R7.2, SW2.2, SW3.2, TP2.1, U1.1 (GND), U1.2 (GND), U1.42 (GND), U1.43 (GND), U1.46 (GND), U1.47 (GND), U1.48 (GND), U1.49 (GND), U1.50 (GND), U1.51 (GND), U1.52 (GND), U1.53 (GND), U1.54 (GND), U1.55 (GND), U1.56 (GND), U1.57 (GND), U1.58 (GND), U1.59 (GND), U1.60 (GND), U1.61 (GND), U1.62 (GND), U1.63 (GND), U1.64 (GND), U1.65 (GND), U2.2 (GND), U3.5 (GND), U4.2 (GND)
IO0_BOOT: R4.2, SW2.1, U1.4 (IO0)
LED_DATA: R8.1, U1.30 (IO48)
LED_DATA_R: D2.3 (DIN), R8.2
Q1_B: Q1.1 (B), R9.2
USB_D+: J1.A6 (D+), J1.B6 (D+), U1.24 (USB_D+), U4.1 (I/O1), U4.6 (I/O1)
USB_D-: J1.A7 (D-), J1.B7 (D-), U1.23 (USB_D-), U4.3 (I/O2), U4.4 (I/O2)
VBUS: F1.1, J1.A4 (VBUS), J1.A9 (VBUS), J1.B4 (VBUS), J1.B9 (VBUS), U4.5 (VBUS)

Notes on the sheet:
USB-C input & 3.3 V regulator
ESP32-S3-MINI-1 module, boot
DMX512 output (RS-485, 3.3 V transceiver)
User interface: RGB status LED, user button, alarm buzzer
Test pads: I2C expansion (RTC / sensor)
No mounting holes: the XLR flange (2x M3) mounts the board in its enclosure.
Buzzer is off-board on the mini: wire a passive magnetic buzzer between BZ+ and BZ- pads.

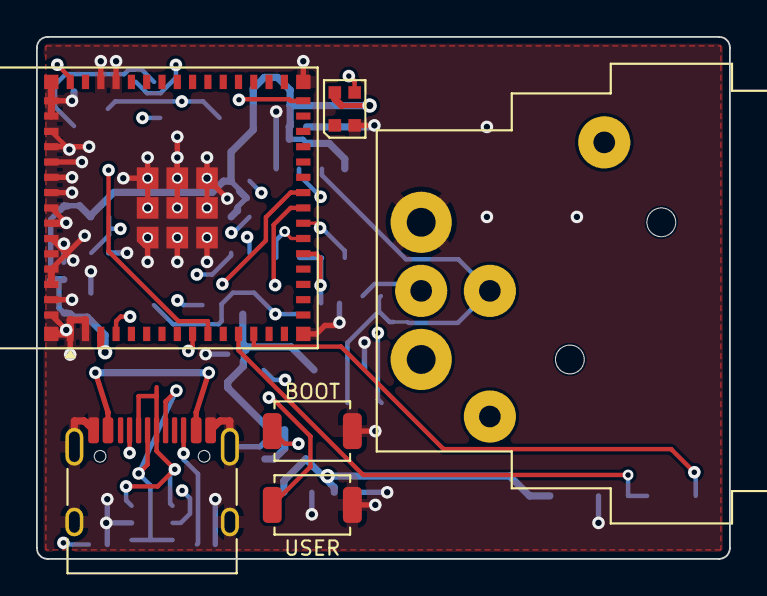
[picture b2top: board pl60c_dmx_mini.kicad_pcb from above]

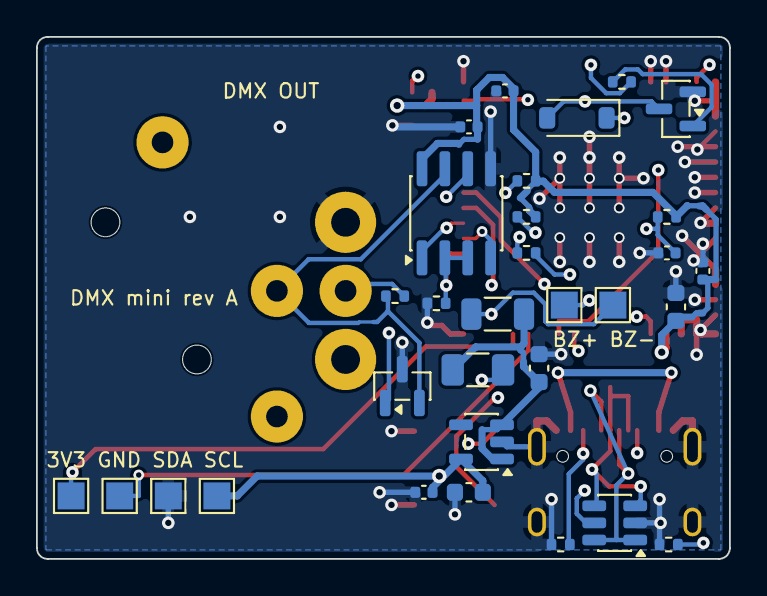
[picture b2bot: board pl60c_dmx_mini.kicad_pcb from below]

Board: 4 copper layers, 38.5 x 29.0 mm, 37 parts (31 on the bottom side), 24 nets.

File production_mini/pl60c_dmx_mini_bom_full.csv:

Ref,Value,MPN,LCSC,Footprint,DNP,Description
C1,10uF,,C19702,Capacitor_SMD:C_0603_1608Metric,,10uF 10V X5R 0603
C2,10uF,,C19702,Capacitor_SMD:C_0603_1608Metric,,10uF 10V X5R 0603
C3,100nF,,C1525,Capacitor_SMD:C_0402_1005Metric,,100nF 16V X7R 0402
C4,10uF,,C19702,Capacitor_SMD:C_0603_1608Metric,,10uF 10V X5R 0603
C5,100nF,,C1525,Capacitor_SMD:C_0402_1005Metric,,100nF 16V X7R 0402
C6,1uF,,C52923,Capacitor_SMD:C_0402_1005Metric,,1uF 25V X5R 0402 (EN reset delay)
C7,100nF,,C1525,Capacitor_SMD:C_0402_1005Metric,,100nF 16V X7R 0402
C8,100nF,,C1525,Capacitor_SMD:C_0402_1005Metric,,100nF 16V X7R 0402
D1,PSM712,PSM712-LF-T7,C32677,Package_TO_SOT_SMD:SOT-23,,RS-485 TVS array +12/-7 V SOT-23
D2,WS2812B-2020,WS2812B-2020-V6,C52917434,LED_SMD:LED_WS2812B-2020_PLCC4_2.0x2.0mm,,Addressable RGB LED 2x2 mm (powered from 3V3 as on Espressif devkits)
D3,B5819W,B5819W SL,C8598,Diode_SMD:D_SOD-123,,Schottky flyback diode SOD-123
F1,1A PTC,BSMD1206-100-30V,C5358568,Fuse:Fuse_1206_3216Metric,,"PTC resettable fuse 1206, 1 A hold / 1.8 A trip"
J1,USB-C 16P,TYPE-C-31-M-12,C165948,Connector_USB:USB_C_Receptacle_HRO_TYPE-C-31-M-12,,"USB-C receptacle 16P, USB 2.0 (HRO TYPE-C-31-M-12)"
J2,XLR-5 female (DMX OUT),NC5FAH,C368501,Connector_Audio:Jack_XLR_Neutrik_NC5FAH_Horizontal,,"Neutrik XLR 5-pin female, horizontal PCB mount (DMX OUT)"
Q1,S8050,S8050,C2146,Package_TO_SOT_SMD:SOT-23,,NPN 0.5A SOT-23 buzzer driver
R1,5.1k,,C25905,Resistor_SMD:R_0402_1005Metric,,5.1k 0402 1% (USB-C CC pull-down)
R2,5.1k,,C25905,Resistor_SMD:R_0402_1005Metric,,5.1k 0402 1% (USB-C CC pull-down)
R3,10k,,C25744,Resistor_SMD:R_0402_1005Metric,,10k 0402
R4,10k,,C25744,Resistor_SMD:R_0402_1005Metric,,10k 0402
R5,10k,,C25744,Resistor_SMD:R_0402_1005Metric,,10k 0402
R6,120R,,C25079,Resistor_SMD:R_0402_1005Metric,yes,120R termination - DNP
R7,10k,,C25744,Resistor_SMD:R_0402_1005Metric,,10k 0402 (DE pull-down)
R8,330R,,C25104,Resistor_SMD:R_0402_1005Metric,,330R 0402 series (WS2812 data)
R9,470R,,C25117,Resistor_SMD:R_0402_1005Metric,,470R 0402 base resistor
R10,10R,,C17903,Resistor_SMD:R_1206_3216Metric,,10R 1206 250mW buzzer series resistor
SW2,BOOT,TS-1088-AR02016,C720477,Button_Switch_SMD:SW_SPST_TS-1088-xR020,,Tactile switch 3.9x3x2 mm SMD
SW3,USER,TS-1088-AR02016,C720477,Button_Switch_SMD:SW_SPST_TS-1088-xR020,,Tactile switch 3.9x3x2 mm SMD (snooze / manual on)
TP1,+3V3,,,TestPoint:TestPoint_Pad_1.5x1.5mm,,Test pad 1.5 mm
TP2,GND,,,TestPoint:TestPoint_Pad_1.5x1.5mm,,Test pad 1.5 mm
TP3,EXP_SDA,,,TestPoint:TestPoint_Pad_1.5x1.5mm,,Test pad 1.5 mm
TP4,EXP_SCL,,,TestPoint:TestPoint_Pad_1.5x1.5mm,,Test pad 1.5 mm
TP5,BZ+,,,TestPoint:TestPoint_Pad_1.5x1.5mm,,External buzzer pad (+5V via 10R)
TP6,BZ-,,,TestPoint:TestPoint_Pad_1.5x1.5mm,,External buzzer pad (driver collector)
U1,ESP32-S3-MINI-1-N8,ESP32-S3-MINI-1-N8,C2913206,RF_Module:ESP32-S2-MINI-1,,"ESP32-S3 module 15.4x20.5 mm, 8 MB flash, PCB antenna (same land pattern as ESP32-S2-MINI-1)"
U2,AP2112K-3.3,AP2112K-3.3TRG1,C51118,Package_TO_SOT_SMD:SOT-23-5,,LDO 3.3V 600mA SOT-23-5
U3,SP3485EN,SP3485EN-L/TR,C8963,Package_SO:SOIC-8_3.9x4.9mm_P1.27mm,,RS-485 transceiver 3.3 V half-duplex SOIC-8
U4,USBLC6-2SC6,USBLC6-2SC6,C7519,Package_TO_SOT_SMD:SOT-23-6,,USB ESD protection array
